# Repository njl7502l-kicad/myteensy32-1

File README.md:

View this project on [CADLAB.io](https://cadlab.io/project/23277). 

# myteensy32-1

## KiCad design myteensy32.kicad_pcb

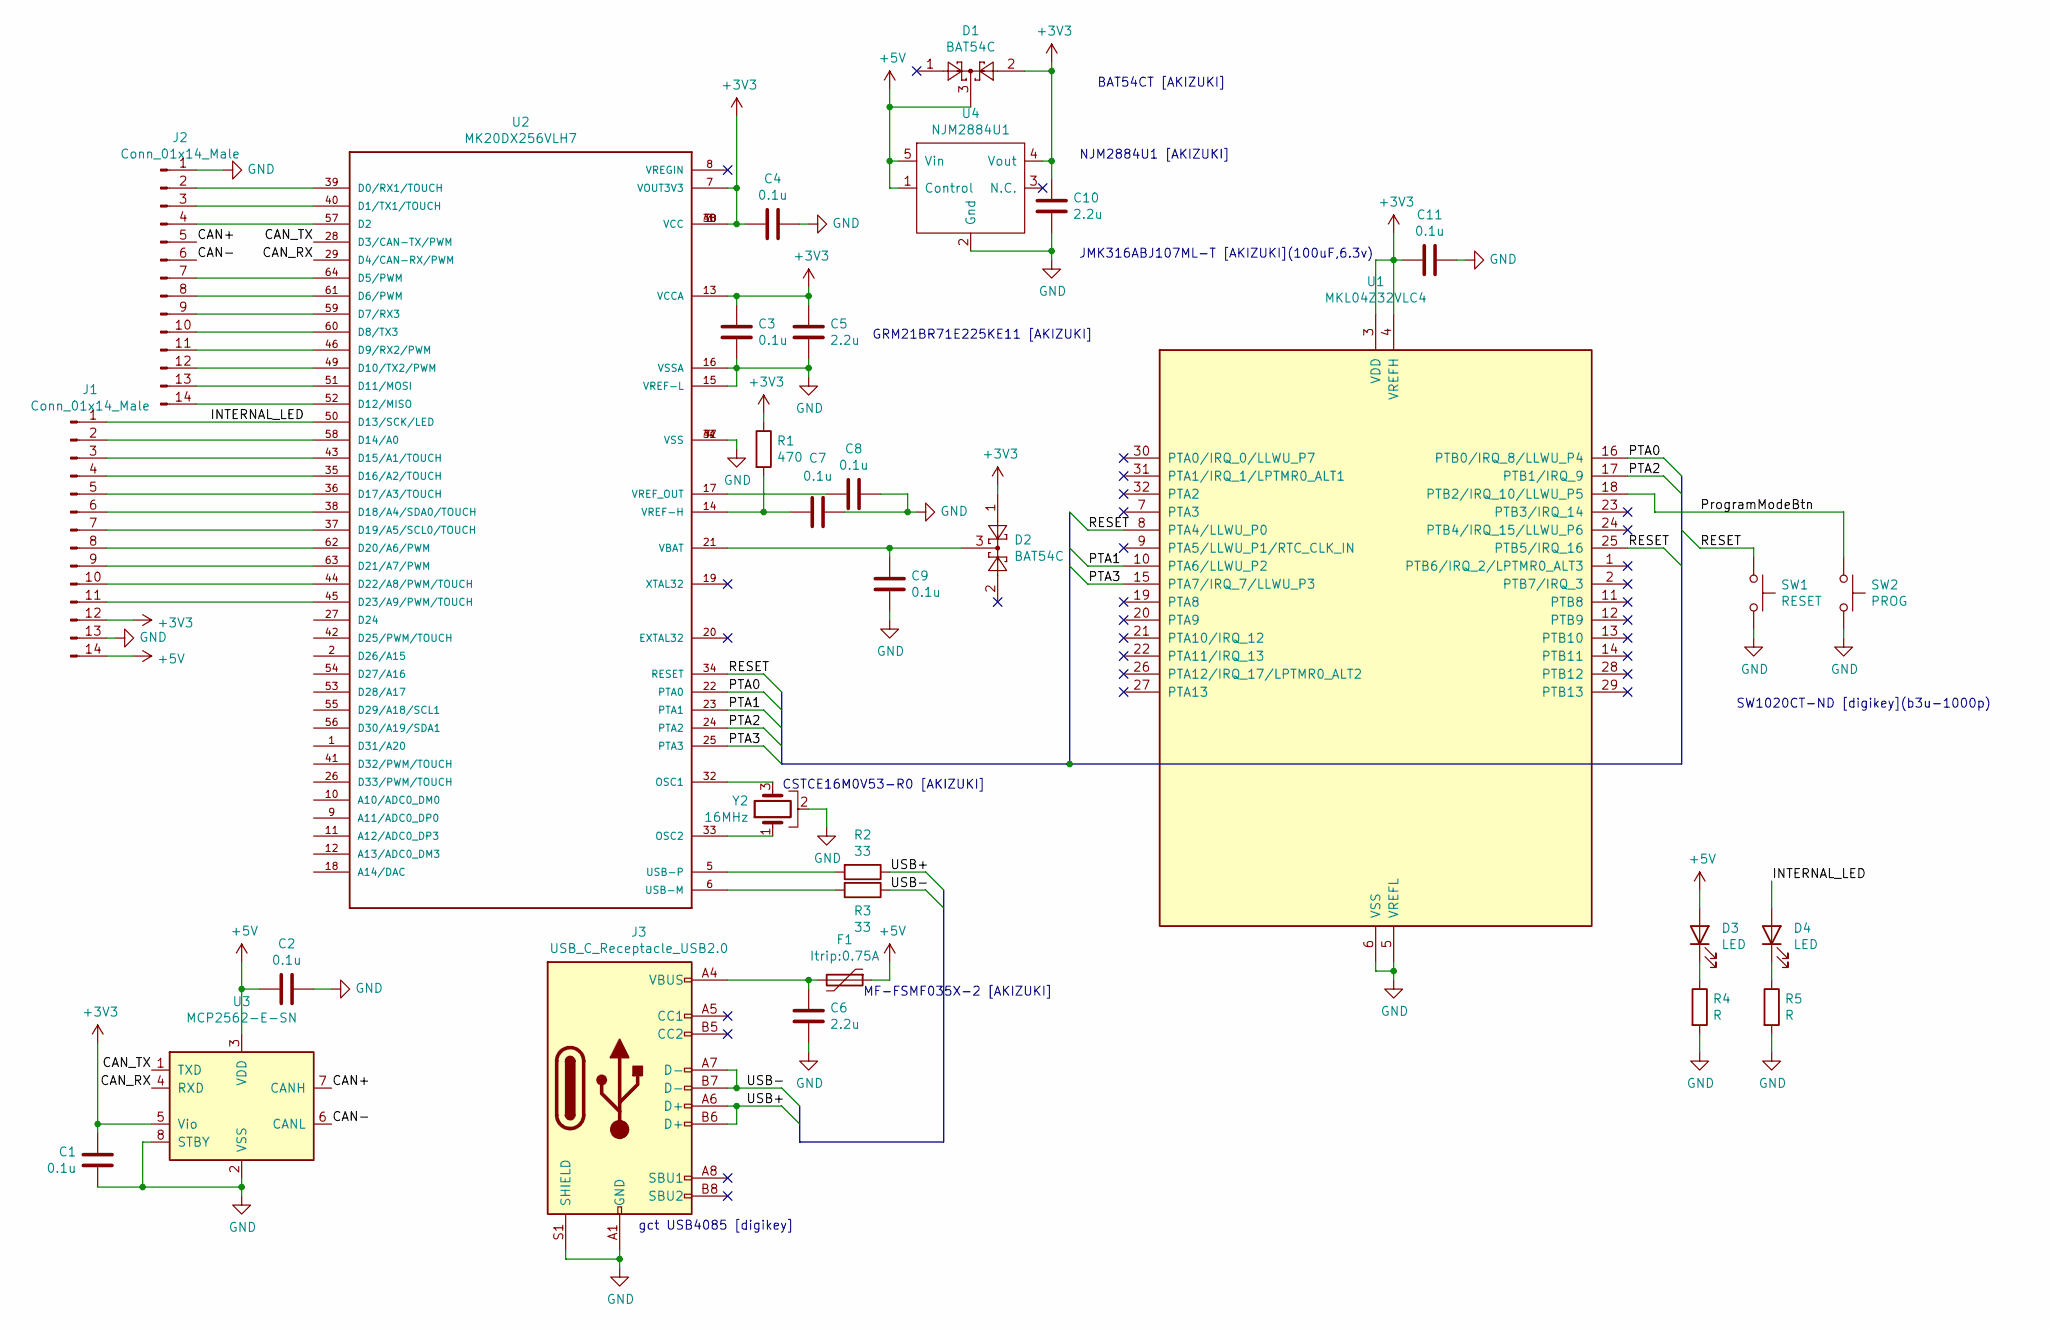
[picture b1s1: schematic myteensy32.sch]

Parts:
C1, C2, C3, C4, C7, C8, C9, C11: 0.1u; C_0603_1608Metric
C5, C6, C10: 2.2u; C_0805_2012Metric
D1, D2: BAT54C; SOT-23
D3, D4: LED; LED_1608_point
F1: Itrip:0.75A; Fuse_0603_1608Metric
J1, J2: Conn_01x14_Male; PinHeader_1x14_P2.54mm_Vertical
J3: USB_C_Receptacle_USB2.0; USB_C_Receptacle_GCT_USB4085
R1: 470; R_0603_1608Metric
R2, R3: 33; R_0603_1608Metric
R4, R5: R; R_0603_1608Metric
SW1: RESET; SW_SPST_B3U-1000P
SW2: PROG; SW_SPST_B3U-1000P
U1: MKL04Z32VLC4; LQFP-32_7x7mm_P0.8mm
U2: MK20DX256VLH7; QFP50P1200X1200X160-64N
U3: MCP2562-E-SN; SOIC-8_3.9x4.9mm_P1.27mm
U4: NJM2884U1; SOT-89-5
Y2: 16MHz; CSTCE16M0V53-R0

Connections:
+3V3: C1.2, C3.2, C4.2, C5.1, C10.1, C11.2, D1.2, D2.1, J1.12, R1.1, U1.3 (VDD), U1.4 (VREFH), U2.3 (VCC), U2.7 (VOUT3V3), U2.13 (VCCA), U2.30 (VCC), U2.48 (VCC), U3.5 (Vio), U4.4 (Vout)
+5V: C2.2, D1.3, D3.2 (A), F1.1, J1.14, U3.3 (VDD), U4.1 (Control), U4.5 (Vin)
/CAN+: J2.5, U3.7 (CANH)
/CAN-: J2.6, U3.6 (CANL)
/CAN_RX: U2.29 (D4/CAN-RX/PWM), U3.4 (RXD)
/CAN_TX: U2.28 (D3/CAN-TX/PWM), U3.1 (TXD)
/INTERNAL_LED: D4.2 (A), J1.1, U2.50 (D13/SCK/LED)
/PTA0: U1.16 (PTB0/IRQ_8/LLWU_P4), U2.22 (PTA0)
/PTA1: U1.10 (PTA6/LLWU_P2), U2.23 (PTA1)
/PTA2: U1.17 (PTB1/IRQ_9), U2.24 (PTA2)
/PTA3: U1.15 (PTA7/IRQ_7/LLWU_P3), U2.25 (PTA3)
/ProgramModeBtn: SW2.1, U1.18 (PTB2/IRQ_10/LLWU_P5)
/RESET: SW1.1, U1.8 (PTA4/LLWU_P0), U1.25 (PTB5/IRQ_16), U2.34 (RESET)
/USB+: J3.A6 (D+), J3.B6 (D+), R2.1
/USB-: J3.A7 (D-), J3.B7 (D-), R3.1
GND: C1.1, C2.1, C3.1, C4.1, C5.2, C6.1, C7.1, C8.1, C9.2, C10.2, C11.1, J1.13, J2.1, J3.A1 (GND), J3.A12 (GND), J3.B1 (GND), J3.B12 (GND), J3.S1 (SHIELD), R4.2, R5.2, SW1.2, SW2.2, U1.5 (VREFL), U1.6 (VSS), U2.4 (VSS), U2.15 (VREF-L), U2.16 (VSSA), U2.31 (VSS), U2.47 (VSS), U3.2 (VSS), U3.8 (STBY), U4.2 (Gnd), Y2.2
unnamed: C6.2, F1.2, J3.A4 (VBUS), J3.A9 (VBUS), J3.B4 (VBUS), J3.B9 (VBUS)
unnamed: C7.2, R1.2, U2.14 (VREF-H)
unnamed: C8.2, U2.17 (VREF_OUT)
unnamed: C9.1, D2.3, U2.21 (VBAT)
unnamed: D3.1 (K), R4.1
unnamed: D4.1 (K), R5.1
unnamed: J1.2, U2.58 (D14/A0)
unnamed: J1.3, U2.43 (D15/A1/TOUCH)
unnamed: J1.4, U2.35 (D16/A2/TOUCH)
unnamed: J1.5, U2.36 (D17/A3/TOUCH)
unnamed: J1.6, U2.38 (D18/A4/SDA0/TOUCH)
unnamed: J1.7, U2.37 (D19/A5/SCL0/TOUCH)
unnamed: J1.8, U2.62 (D20/A6/PWM)
unnamed: J1.9, U2.63 (D21/A7/PWM)
unnamed: J1.10, U2.44 (D22/A8/PWM/TOUCH)
unnamed: J1.11, U2.45 (D23/A9/PWM/TOUCH)
unnamed: J2.2, U2.39 (D0/RX1/TOUCH)
unnamed: J2.3, U2.40 (D1/TX1/TOUCH)
unnamed: J2.4, U2.57 (D2)
unnamed: J2.7, U2.64 (D5/PWM)
unnamed: J2.8, U2.61 (D6/PWM)
unnamed: J2.9, U2.59 (D7/RX3)
unnamed: J2.10, U2.60 (D8/TX3)
unnamed: J2.11, U2.46 (D9/RX2/PWM)
unnamed: J2.12, U2.49 (D10/TX2/PWM)
unnamed: J2.13, U2.51 (D11/MOSI)
unnamed: J2.14, U2.52 (D12/MISO)
unnamed: R2.2, U2.5 (USB-P)
unnamed: R3.2, U2.6 (USB-M)
unnamed: U2.32 (OSC1), Y2.3
unnamed: U2.33 (OSC2), Y2.1

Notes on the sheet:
CSTCE16M0V53-R0 [AKIZUKI]
gct USB4085 [digikey]
MF-FSMF035X-2 [AKIZUKI]
NJM2884U1 [AKIZUKI]
BAT54CT [AKIZUKI]
SW1020CT-ND [digikey](b3u-1000p)
GRM21BR71E225KE11 [AKIZUKI]
JMK316ABJ107ML-T [AKIZUKI](100uF,6.3v)

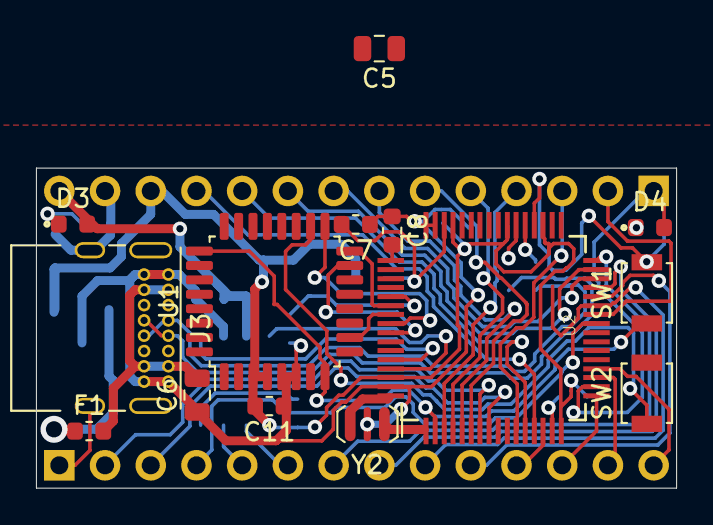
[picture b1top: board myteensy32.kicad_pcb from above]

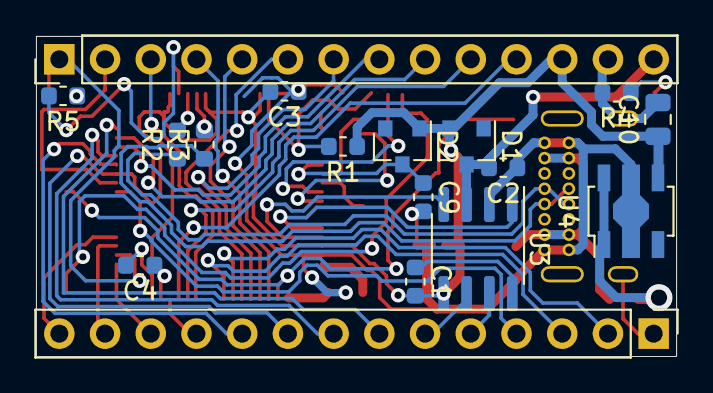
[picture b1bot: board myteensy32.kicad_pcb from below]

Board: 2 copper layers, 35.6 x 17.8 mm, 31 parts (17 on the bottom side), 47 nets.

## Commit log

2020-08-29 init
2020-08-29 submodule add kicad
2020-08-29 add sym-lib-table kicad
2020-08-29 add fp-lib-table kicad
2020-08-29 mkl04z32vlc4を追加
2020-08-29 add sym mk20dx256vlh7
2020-08-29 mk20dx256vlh7を入れ直し
2020-08-29 シンボルのの作り方が雑だったので心配したけど大丈夫そうだった。
2020-08-29 mkl04z32vlc4周辺の配線ができた
2020-08-29 usb,Crystal等周辺回路の追加
2020-08-29 ラベルのつもりがテキストになってたので修正
2020-08-29 usb周辺回路、agnd等を記述
2020-08-30 とりあえず全部の素子にフットプリントを割り当てて大きさの余裕を見る。
2020-08-30 teensy3.2のサイズに収めようとしたけどかなり難しい
2020-08-30 いったん配線を全削除
2020-08-30 配線幅を変えたら希望が見えてきた
2020-08-30 rtc用の水晶は面積の問題と使わないので削除
2020-08-30 回路図中のレギュレータを変更
2020-08-30 固まったのでバックアップ
2020-08-30 許容クリアランスをfusionPCBの規約に沿ってギリギリに変更
2020-08-30 いったん保存
2020-08-30 殆どの配線が終わった。
2020-08-31 いったんコミット
2020-09-01 Backlink to CADLAB.io has been added.
